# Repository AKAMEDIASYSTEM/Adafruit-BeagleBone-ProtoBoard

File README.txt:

Hi, I'm hoping to do a number of Beaglebone Black projects that use a lot of I2C and analog sensing devices. I modified Adafruit's excellent Proto Capes to include a dedicated I2C bus area that allows you to connect up to 11 I2C devices to the same bus; also, in the place where the SMD pads were, I made an area where you can easily connect voltage-divider type analog sensors to a0 through a5.

I also added some BBB-specific pin labels to the boead because I found I kept having to look those up...

- AKA

PS, super-thanks to Adafruit for sharing their design!

== Adafruit's original text ==

Adafruit Proto Cape Kit for Beagle Bone 

These are the Eagle CAD files for the Adafruit Proto Cape Kit for Beagle Bone:
  ----> http://www.adafruit.com/products/572

Adafruit invests time and resources providing this open source design, please support Adafruit and open-source hardware by purchasing products from Adafruit!

Add some circuitry to your Beagle Bone with our lovely Proto Cape. If you have a 'Bone you need one of these! This PCB fits neatly on top of a Beagle Bone, without getting in the way of the Ethernet jack, and provides a breakout to both 46 pin headers - with individual numbering to keep them straight. We also threw down some strips to access the 5V and 3V power supplies as well as two SMT breakouts, one for SOIC-8's and one for SOT-23's. 

Kit comes with a double-sided FR4 PCB and 3 sticks of header. You'll need to place the header into the Beagle Bone and then solder the Proto Cape PCB in place, but its very easy and should take only 10 minutes max even for beginners

All text above must be included in any redistribution

Designed by Limor Fried/Ladyada and Kevin Townsend for Adafruit Industries.
Creative Commons Attribution/Share-Alike, all text above must be included in any redistribution

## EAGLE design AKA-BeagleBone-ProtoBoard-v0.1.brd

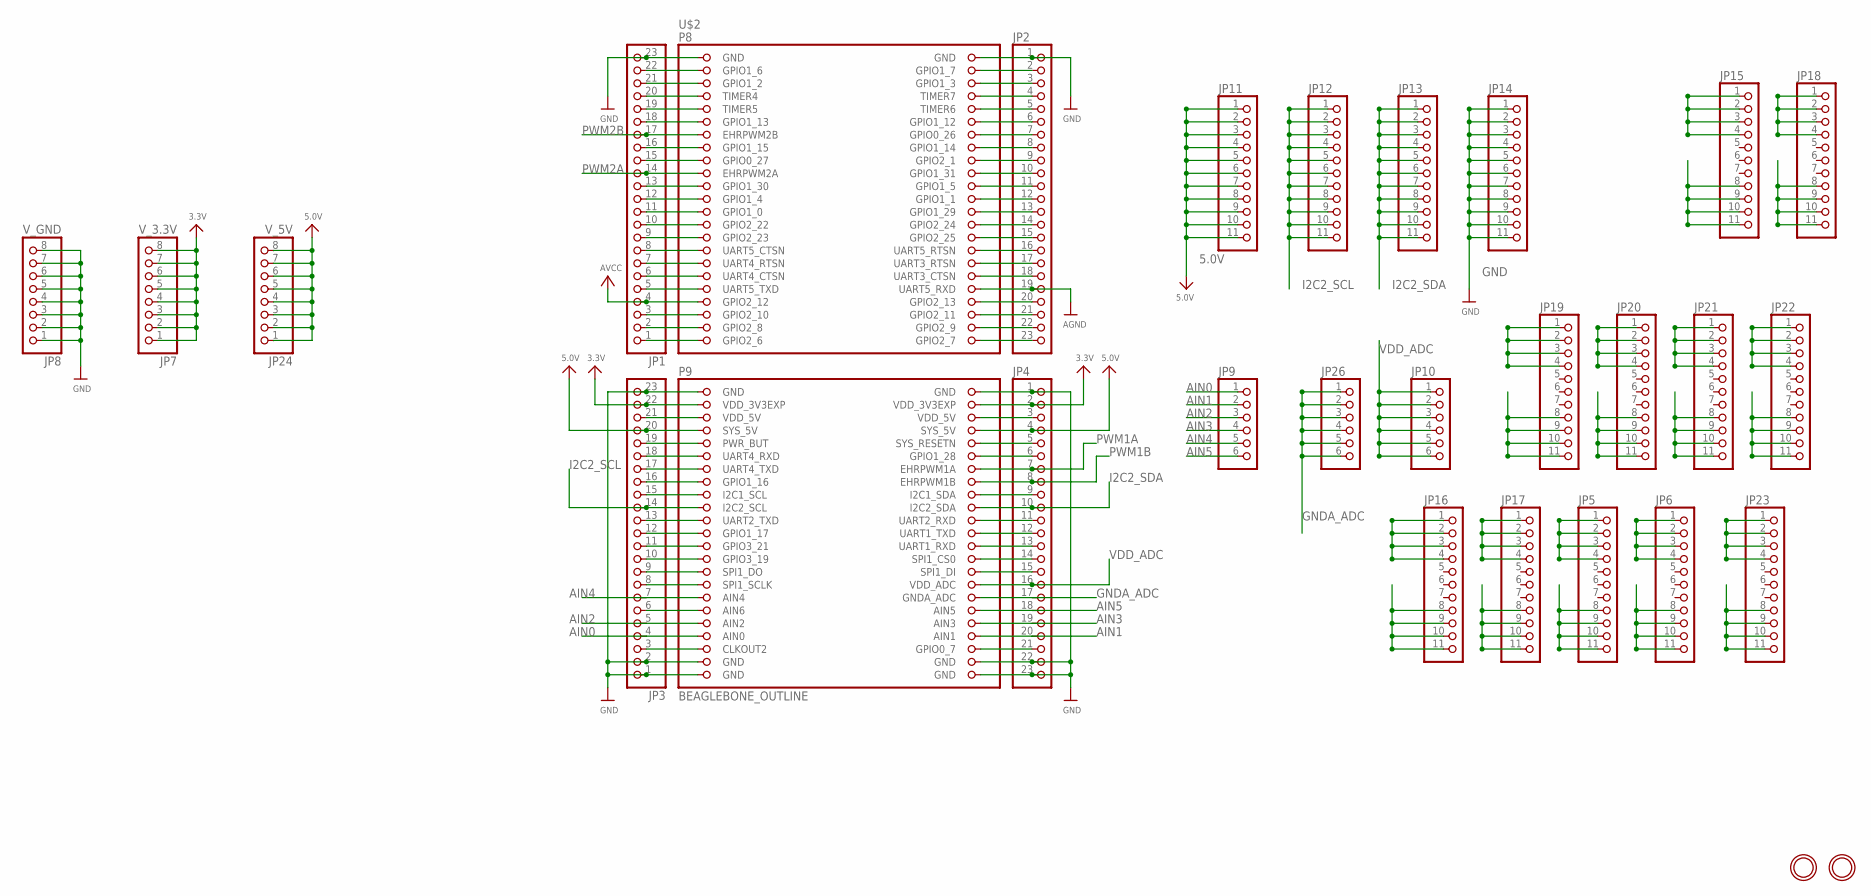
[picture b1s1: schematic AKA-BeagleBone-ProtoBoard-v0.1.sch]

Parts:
JP1, JP2, JP3, JP4: HEADER-1X23; 1X23_ROUND_70MIL
JP5, JP6, JP11, JP12, JP13, JP14, JP15, JP16, JP17, JP18, JP19, JP20, JP21, JP22, JP23: HEADER-1X1176MIL; 1X11_ROUND_76
JP7: V_3.3V; 1X08_ROUND_70
JP8: V_GND; 1X08_ROUND_70
JP9, JP10, JP26: HEADER-1X676MIL; 1X06_ROUND_76
JP24: V_5V; 1X08_ROUND_70
U$2: BEAGLEBONE_OUTLINE; BEAGLEBONE_SHIELD
U$22, U$23: MOUNTINGHOLE3.0THIN; MOUNTINGHOLE_3.0_PLATEDTHIN

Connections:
3.3V: JP3.22, JP4.2, JP7.1, JP7.2, JP7.3, JP7.4, JP7.5, JP7.6, JP7.7, JP7.8, U$2.49 (VDD_3V3EXP), U$2.50 (VDD_3V3EXP)
5.0V: JP3.20, JP4.4, JP11.1, JP11.2, JP11.3, JP11.4, JP11.5, JP11.6, JP11.7, JP11.8, JP11.9, JP11.10, JP11.11, JP24.1, JP24.2, JP24.3, JP24.4, JP24.5, JP24.6, JP24.7, JP24.8, U$2.53 (SYS_5V), U$2.54 (SYS_5V)
AGND: JP2.19, U$2.38 (UART5_RXD)
AIN0: JP3.4, JP9.1, U$2.85 (AIN0)
AIN1: JP4.20, JP9.2, U$2.86 (AIN1)
AIN2: JP3.5, JP9.3, U$2.83 (AIN2)
AIN3: JP4.19, JP9.4, U$2.84 (AIN3)
AIN4: JP3.7, JP9.5, U$2.79 (AIN4)
AIN5: JP4.18, JP9.6, U$2.82 (AIN5)
AIN6: JP3.6, U$2.81 (AIN6)
AVCC: JP1.4, U$2.39 (GPIO2_12)
GND: JP1.23, JP2.1, JP3.1, JP3.2, JP3.23, JP4.1, JP4.22, JP4.23, JP8.1, JP8.2, JP8.3, JP8.4, JP8.5, JP8.6, JP8.7, JP8.8, JP14.1, JP14.2, JP14.3, JP14.4, JP14.5, JP14.6, JP14.7, JP14.8, JP14.9, JP14.10, JP14.11, U$2.1 (GND), U$2.2 (GND), U$2.47 (GND), U$2.48 (GND), U$2.89 (GND), U$2.90 (GND), U$2.91 (GND), U$2.92 (GND)
GNDA_ADC: JP4.17, JP26.1, JP26.2, JP26.3, JP26.4, JP26.5, JP26.6, U$2.80 (GNDA_ADC)
I2C2_SCL: JP3.14, JP12.1, JP12.2, JP12.3, JP12.4, JP12.5, JP12.6, JP12.7, JP12.8, JP12.9, JP12.10, JP12.11, U$2.65 (I2C2_SCL)
I2C2_SDA: JP4.10, JP13.1, JP13.2, JP13.3, JP13.4, JP13.5, JP13.6, JP13.7, JP13.8, JP13.9, JP13.10, JP13.11, U$2.66 (I2C2_SDA)
unnamed: JP15.1, JP15.2, JP15.3, JP15.4
unnamed: JP16.1, JP16.2, JP16.3, JP16.4
unnamed: JP17.1, JP17.2, JP17.3, JP17.4
unnamed: JP1.20, U$2.7 (TIMER4)
unnamed: JP1.19, U$2.9 (TIMER5)
unnamed: JP1.18, U$2.11 (GPIO1_13)
unnamed: JP5.1, JP5.2, JP5.3, JP5.4
unnamed: JP1.16, U$2.15 (GPIO1_15)
unnamed: JP1.15, U$2.17 (GPIO0_27)
unnamed: JP18.1, JP18.2, JP18.3, JP18.4
unnamed: JP1.13, U$2.21 (GPIO1_30)
unnamed: JP1.12, U$2.23 (GPIO1_4)
unnamed: JP1.11, U$2.25 (GPIO1_0)
unnamed: JP1.10, U$2.27 (GPIO2_22)
unnamed: JP1.9, U$2.29 (GPIO2_23)
unnamed: JP1.8, U$2.31 (UART5_CTSN)
unnamed: JP1.7, U$2.33 (UART4_RTSN)
unnamed: JP1.6, U$2.35 (UART4_CTSN)
unnamed: JP1.5, U$2.37 (UART5_TXD)
unnamed: JP6.1, JP6.2, JP6.3, JP6.4
unnamed: JP1.3, U$2.41 (GPIO2_10)
unnamed: JP1.2, U$2.43 (GPIO2_8)
unnamed: JP1.1, U$2.45 (GPIO2_6)
unnamed: JP19.1, JP19.2, JP19.3, JP19.4
unnamed: JP20.1, JP20.2, JP20.3, JP20.4
unnamed: JP21.1, JP21.2, JP21.3, JP21.4
unnamed: JP2.4, U$2.8 (TIMER7)
unnamed: JP2.5, U$2.10 (TIMER6)
unnamed: JP2.6, U$2.12 (GPIO1_12)
unnamed: JP2.7, U$2.14 (GPIO0_26)
unnamed: JP2.8, U$2.16 (GPIO1_14)
unnamed: JP2.9, U$2.18 (GPIO2_1)
unnamed: JP2.10, U$2.20 (GPIO1_31)
unnamed: JP2.11, U$2.22 (GPIO1_5)
unnamed: JP2.12, U$2.24 (GPIO1_1)
unnamed: JP2.13, U$2.26 (GPIO1_29)
unnamed: JP2.14, U$2.28 (GPIO2_24)
unnamed: JP2.15, U$2.30 (GPIO2_25)
unnamed: JP2.16, U$2.32 (UART5_RTSN)
unnamed: JP2.17, U$2.34 (UART3_RTSN)
unnamed: JP2.18, U$2.36 (UART3_CTSN)
unnamed: JP22.1, JP22.2, JP22.3, JP22.4
unnamed: JP2.20, U$2.40 (GPIO2_13)
unnamed: JP2.21, U$2.42 (GPIO2_11)
unnamed: JP2.22, U$2.44 (GPIO2_9)
unnamed: JP2.23, U$2.46 (GPIO2_7)
unnamed: JP1.22, U$2.3 (GPIO1_6)
unnamed: JP1.21, U$2.5 (GPIO1_2)
unnamed: JP3.21, U$2.51 (VDD_5V)
unnamed: JP2.2, U$2.4 (GPIO1_7)
unnamed: JP3.19, U$2.55 (PWR_BUT)
unnamed: JP3.18, U$2.57 (UART4_RXD)
unnamed: JP3.17, U$2.59 (UART4_TXD)
unnamed: JP3.16, U$2.61 (GPIO1_16)
unnamed: JP3.15, U$2.63 (I2C1_SCL)
unnamed: JP23.1, JP23.2, JP23.3, JP23.4
unnamed: JP3.13, U$2.67 (UART2_TXD)
unnamed: JP3.12, U$2.69 (GPIO1_17)
unnamed: JP3.11, U$2.71 (GPIO3_21)
unnamed: JP3.10, U$2.73 (GPIO3_19)
unnamed: JP3.9, U$2.75 (SPI1_DO)
unnamed: JP3.8, U$2.77 (SPI1_SCLK)
unnamed: JP3.3, U$2.87 (CLKOUT2)
unnamed: JP2.3, U$2.6 (GPIO1_3)
unnamed: JP4.21, U$2.88 (GPIO0_7)
unnamed: JP4.3, U$2.52 (VDD_5V)
unnamed: JP4.5, U$2.56 (SYS_RESETN)
unnamed: JP4.6, U$2.58 (GPIO1_28)
unnamed: JP4.9, U$2.64 (I2C1_SDA)
unnamed: JP4.11, U$2.68 (UART2_RXD)
unnamed: JP4.12, U$2.70 (UART1_TXD)
unnamed: JP4.13, U$2.72 (UART1_RXD)
unnamed: JP4.14, U$2.74 (SPI1_CS0)
unnamed: JP4.15, U$2.76 (SPI1_DI)
PWM1A: JP4.7, U$2.60 (EHRPWM1A)
PWM1B: JP4.8, U$2.62 (EHRPWM1B)
PWM2A: JP1.14, JP18.8, JP18.9, JP18.10, JP18.11, U$2.19 (EHRPWM2A)
PWM2A1: JP17.8, JP17.9, JP17.10, JP17.11
PWM2A2: JP5.8, JP5.9, JP5.10, JP5.11
PWM2A3: JP6.8, JP6.9, JP6.10, JP6.11
PWM2A4: JP20.8, JP20.9, JP20.10, JP20.11
PWM2A5: JP21.8, JP21.9, JP21.10, JP21.11
PWM2A6: JP22.8, JP22.9, JP22.10, JP22.11
PWM2A7: JP23.8, JP23.9, JP23.10, JP23.11
PWM2B: JP1.17, JP15.8, JP15.9, JP15.10, JP15.11, U$2.13 (EHRPWM2B)
PWM2B1: JP16.8, JP16.9, JP16.10, JP16.11
PWM2B2: JP19.8, JP19.9, JP19.10, JP19.11
VDD_ADC: JP4.16, JP10.1, JP10.2, JP10.3, JP10.4, JP10.5, JP10.6, U$2.78 (VDD_ADC)

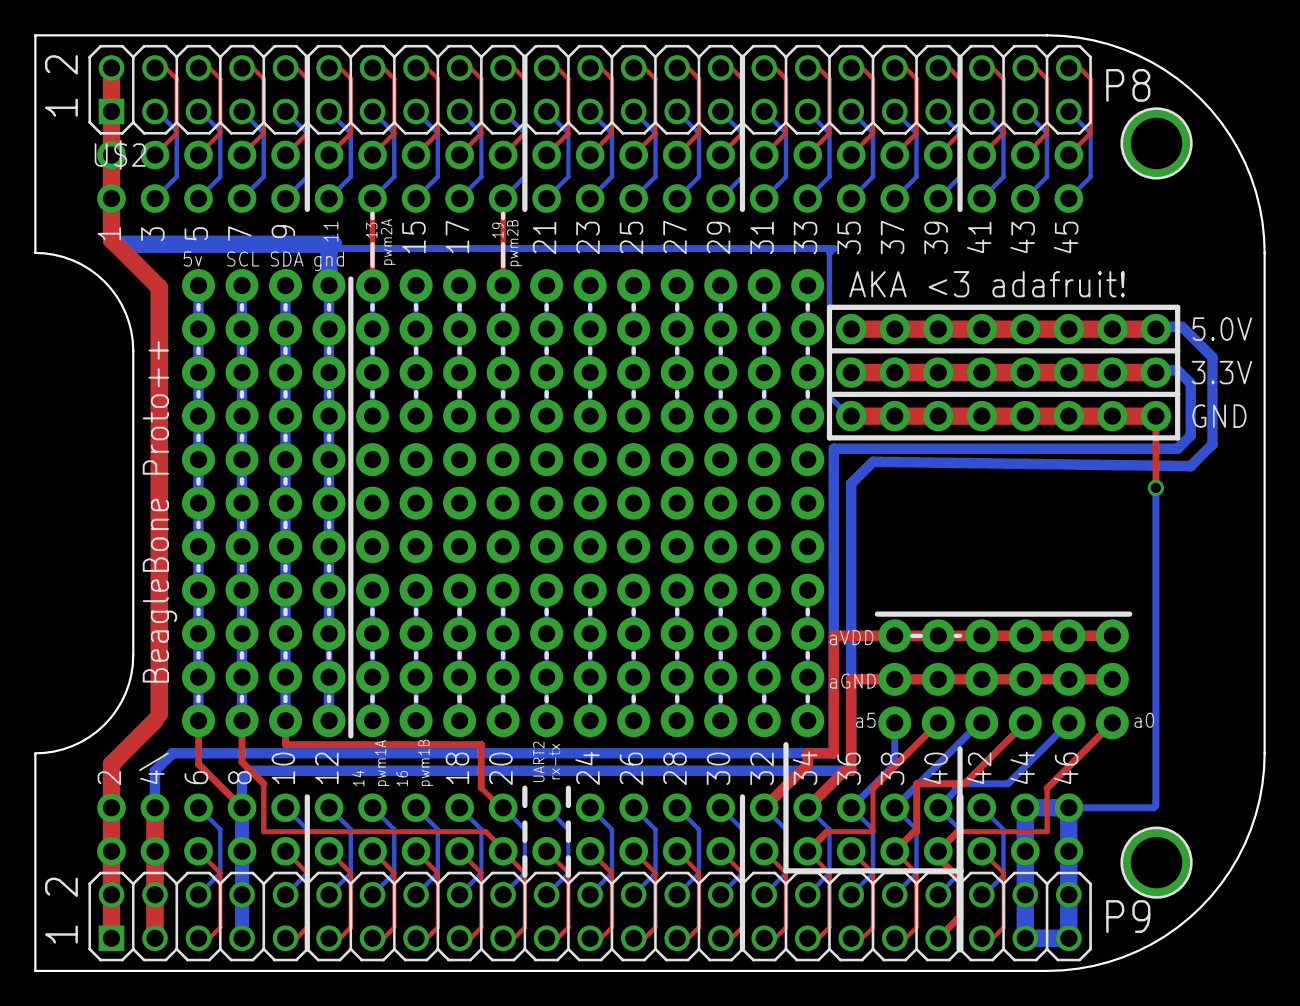
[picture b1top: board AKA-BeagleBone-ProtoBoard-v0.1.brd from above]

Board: 2 copper layers, 71.8 x 54.6 mm, 28 parts (0 on the bottom side), 103 nets.

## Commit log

2014-01-18 added an I2C bus and an analog sensor bus, at the expense of the SMD breakouts
2014-01-18 altered README to describe the changes
2014-01-18 cleaning up files and adding gitignore
